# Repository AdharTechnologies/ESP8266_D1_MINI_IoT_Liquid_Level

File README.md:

# ESP8266_D1_MINI_IoT_Liquid_Level

# Description
This is a ESP8266 D1 Mini based IoT liquid level sensor using Blynk IoT Platform and FS-IR02 optical liquid sensor.
PCB files and code is given. Slight change in the code is needed and you are good to go.

kindly read this blog for full understanding: https://docs.google.com/document/d/e/2PACX-1vTtqNfzRCTwCoMZxVgGbPQqkUs0_NW9okKvrQEpY97LD3bP_43XxNdcu0OOmvAOUq4PffVxorKm6yeB/pub

# Embedded CTG

Facebook:https://web.facebook.com/p/Embedded-CTG-61558436573900/?mibextid=ZbWKwL&_rdc=1&_rdr

Youtube: https://www.youtube.com/@EmbeddedCTG

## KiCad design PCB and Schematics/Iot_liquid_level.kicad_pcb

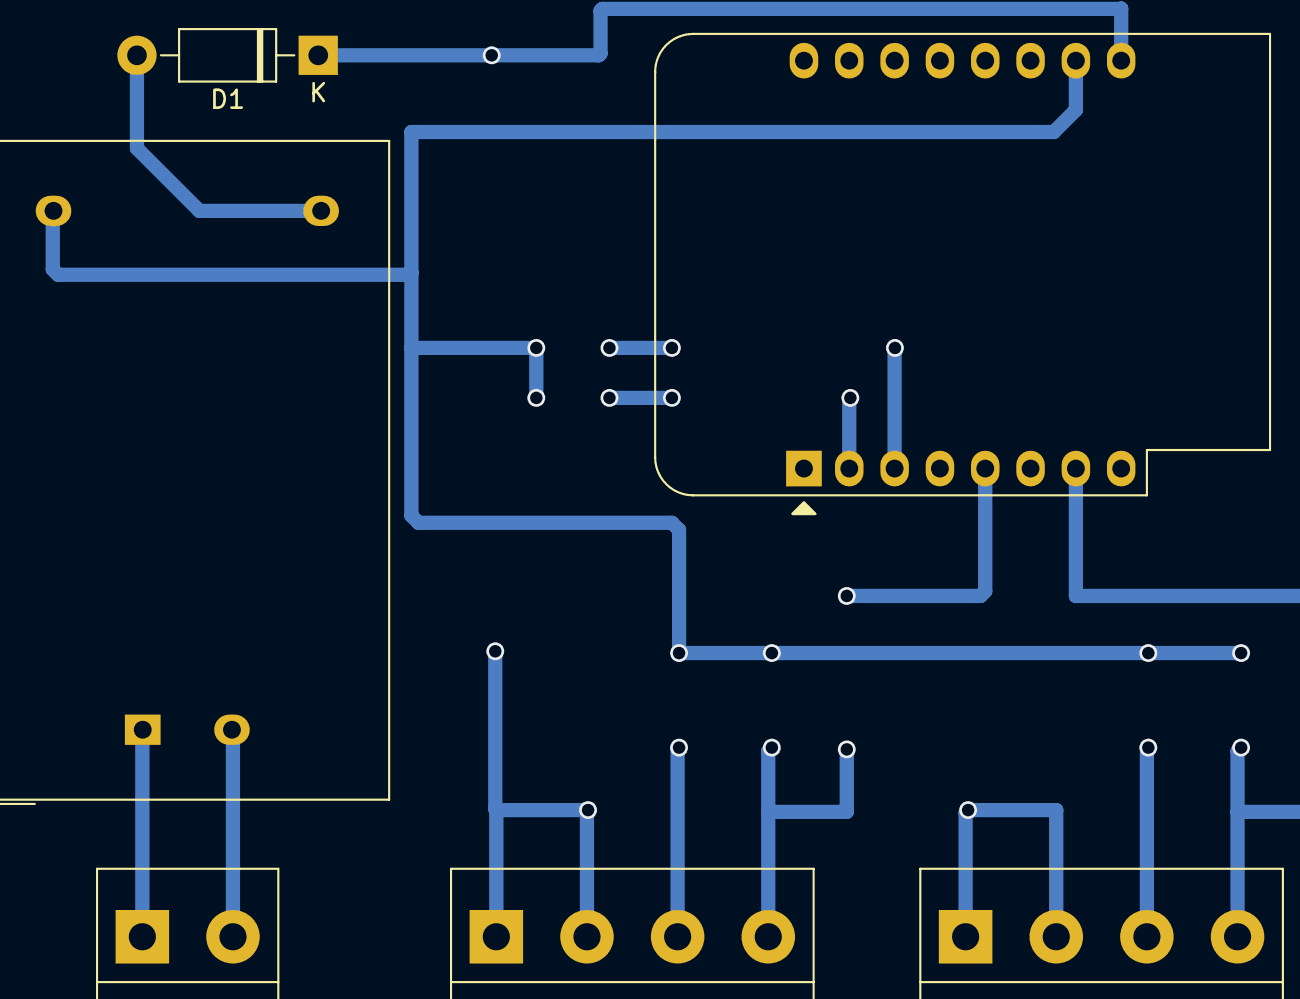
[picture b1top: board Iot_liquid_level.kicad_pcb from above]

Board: 2 copper layers, 3 parts (0 on the bottom side), 3 nets.

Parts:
D1: 1N4007; D_DO-41_SOD81_P10.16mm_Horizontal
PS1: HLK-PM01; Converter_ACDC_Hi-Link_HLK-PMxx
U1: WeMos_D1_mini; WEMOS_D1_mini_light

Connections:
unnamed: D1.2 (A), PS1.4 (+Vout)
unnamed: D1.1 (K), U1.9 (5V)
unnamed: PS1.3 (-Vout), U1.10 (GND)

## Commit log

2024-06-23 README.md
